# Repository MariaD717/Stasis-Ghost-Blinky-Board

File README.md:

# Ghost-Blinky-Board
I am making a blinky board shaped like a ghost, following the starter project guide. This is my first PCB project ever. It is also my second ever hardware project. A lot of my files are named "Phoenix..." because I was originally going to make it the shape of a phoenix, but all the images were too complicated.

# Why?
I am making this project because it is fun. Since I find hardware interesting, I decided this was a good way to learn about it.

# 3D

# JLPCB 

# KiCad

Schematic

PCB

# BoM

Link to my [BoM](https://github.com/MariaD717/Stasis-Ghost-Blinky-Board/blob/main/BoM.csv)

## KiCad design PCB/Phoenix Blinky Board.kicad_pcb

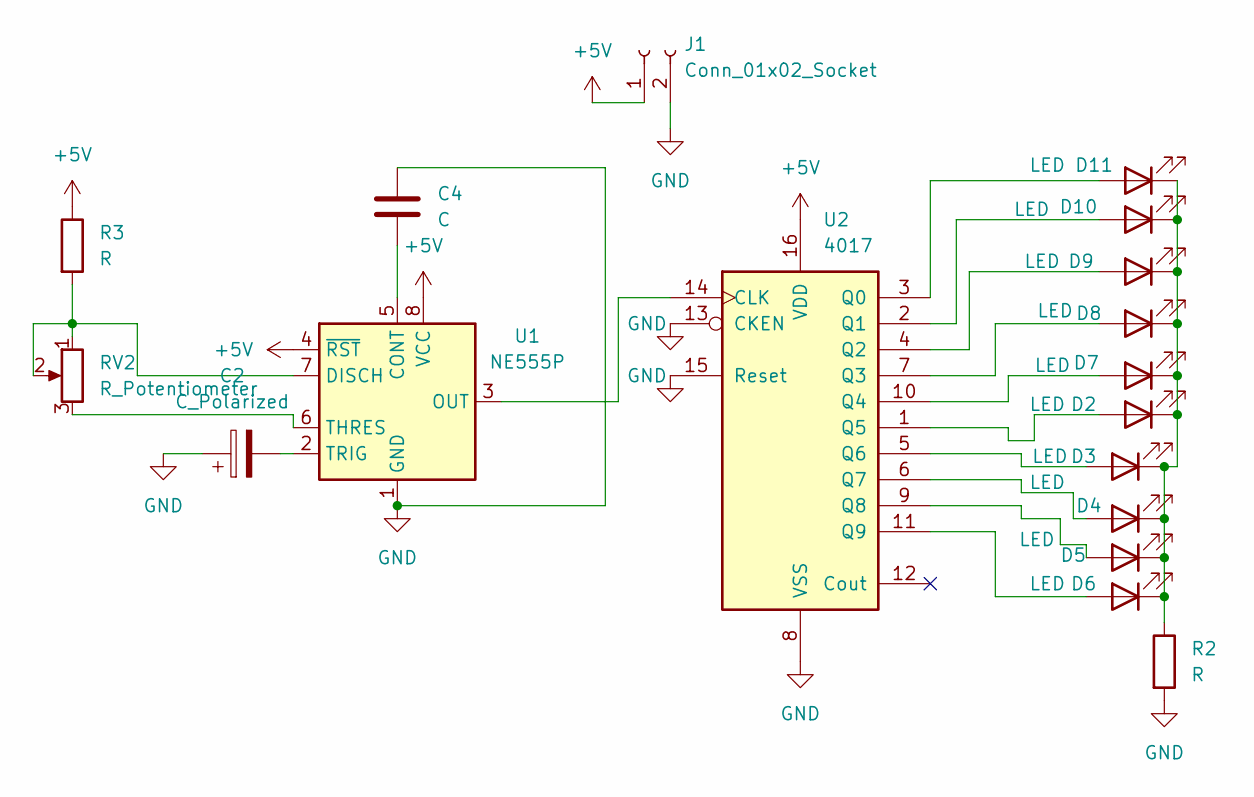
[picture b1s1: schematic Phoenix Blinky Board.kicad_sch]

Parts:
C2: C_Polarized; CP_Radial_D5.0mm_P2.00mm
C4: C; C_Disc_D7.5mm_W2.5mm_P5.00mm
D2, D3, D4, D5, D6, D7, D8, D9, D10, D11: LED; LED_D3.0mm
J1: Conn_01x02_Socket; PinHeader_1x02_P2.54mm_Vertical
R2, R3: R; R_Axial_DIN0207_L6.3mm_D2.5mm_P7.62mm_Horizontal
RV2: R_Potentiometer; Potentiometer_Vishay_T93YA_Vertical
U1: NE555P; DIP-8_W7.62mm
U2: 4017; N16

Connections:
+5V: J1.1, R3.1, U1.4 (~RST), U1.8 (VCC), U2.16 (VDD)
GND: C2.1, C4.2, J1.2, R2.2, U1.1 (GND), U2.8 (VSS), U2.13 (CKEN), U2.15 (Reset)
unnamed: D2.2 (A), U2.1 (Q5)
unnamed: D3.2 (A), U2.5 (Q6)
unnamed: D4.2 (A), U2.6 (Q7)
unnamed: D5.2 (A), U2.9 (Q8)
unnamed: D6.2 (A), U2.11 (Q9)
unnamed: D7.2 (A), U2.10 (Q4)
unnamed: D8.2 (A), U2.7 (Q3)
unnamed: D9.2 (A), U2.4 (Q2)
unnamed: D10.2 (A), U2.2 (Q1)
unnamed: D2.1 (K), D3.1 (K), D4.1 (K), D5.1 (K), D6.1 (K), D7.1 (K), D8.1 (K), D9.1 (K), D10.1 (K), D11.1 (K), R2.1
unnamed: D11.2 (A), U2.3 (Q0)
unnamed: C4.1, U1.5 (CONT)
unnamed: R3.2, RV2.1, RV2.2, U1.7 (DISCH)
unnamed: U1.3 (OUT), U2.14 (CLK)
unnamed: RV2.3, U1.6 (THRES)
unnamed: C2.2, U1.2 (TRIG)

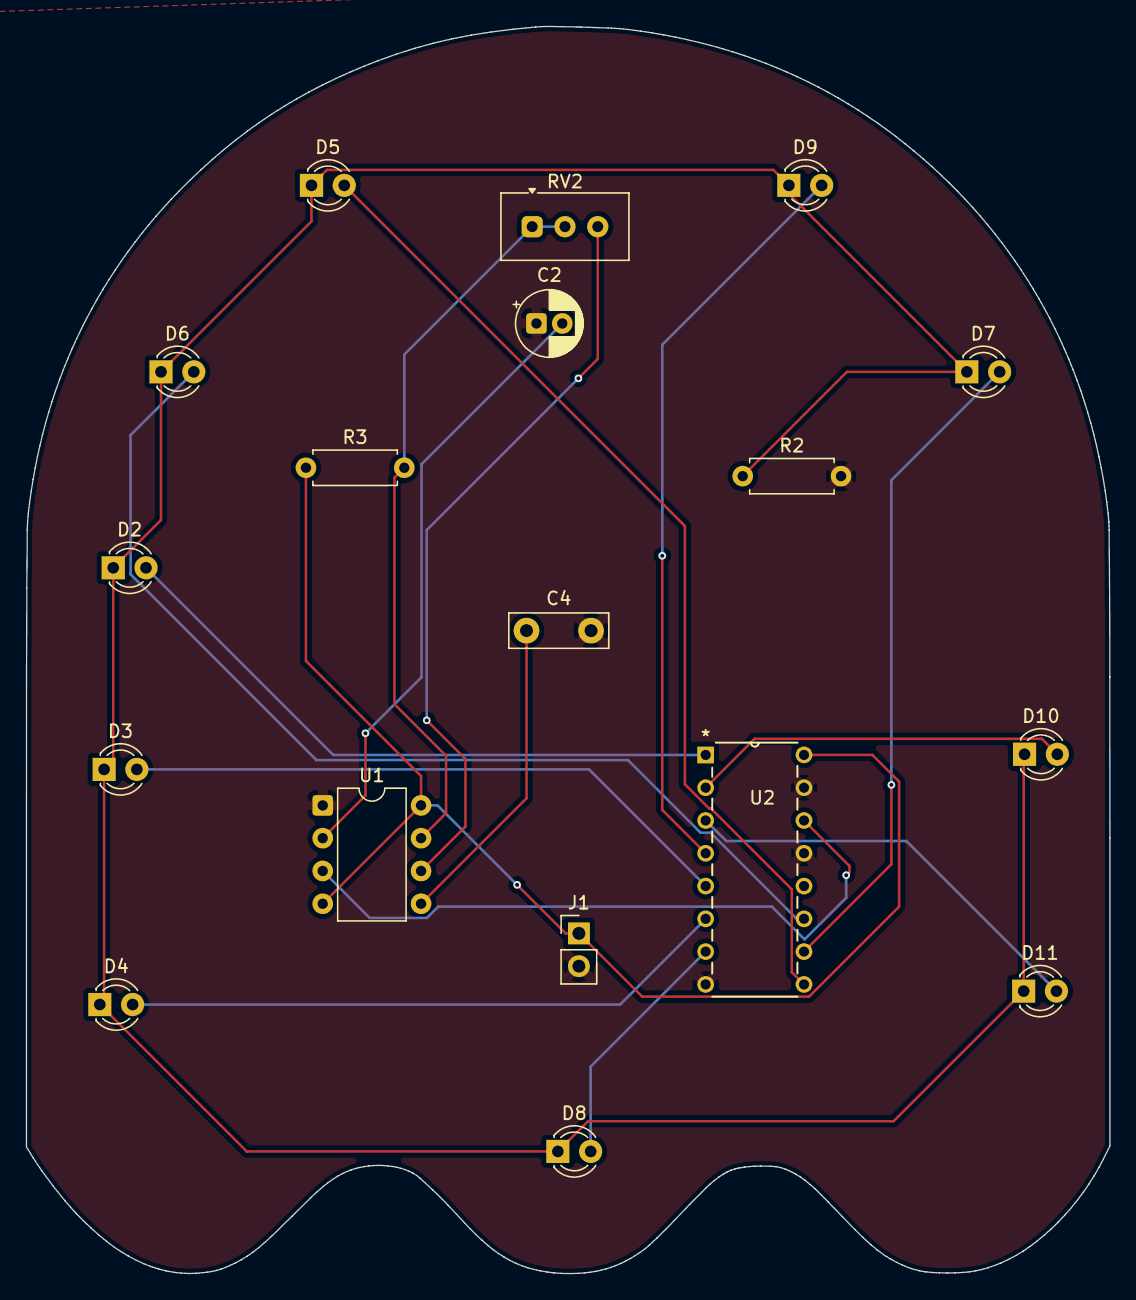
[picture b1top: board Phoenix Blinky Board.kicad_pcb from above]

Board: 2 copper layers, 83.9 x 96.6 mm, 18 parts (0 on the bottom side), 18 nets.

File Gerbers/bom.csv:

Designator,Footprint,Quantity,Value,LCSC Part #
C2,CP_Radial_D5.0mm_P2.00mm,1,C_Polarized,
C4,C_Disc_D7.5mm_W2.5mm_P5.00mm,1,C,
"D10, D11, D2, D3, D4, D5, D6, D7, D8, D9",LED_D3.0mm,10,LED,
J1,PinHeader_1x02_P2.54mm_Vertical,1,Conn_01x02_Socket,
"R2, R3",R_Axial_DIN0207_L6.3mm_D2.5mm_P7.62mm_Horizontal,2,R,
RV2,Potentiometer_Vishay_T93YA_Vertical,1,R_Potentiometer,
U1,DIP-8_W7.62mm,1,NE555P,
U2,N16,1,4017,

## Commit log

2026-05-01 Rearrange files
2026-05-01 Add images to README.md
2026-05-02 Move files
2026-05-03 Gerbers
2026-05-04 Move gerbers
